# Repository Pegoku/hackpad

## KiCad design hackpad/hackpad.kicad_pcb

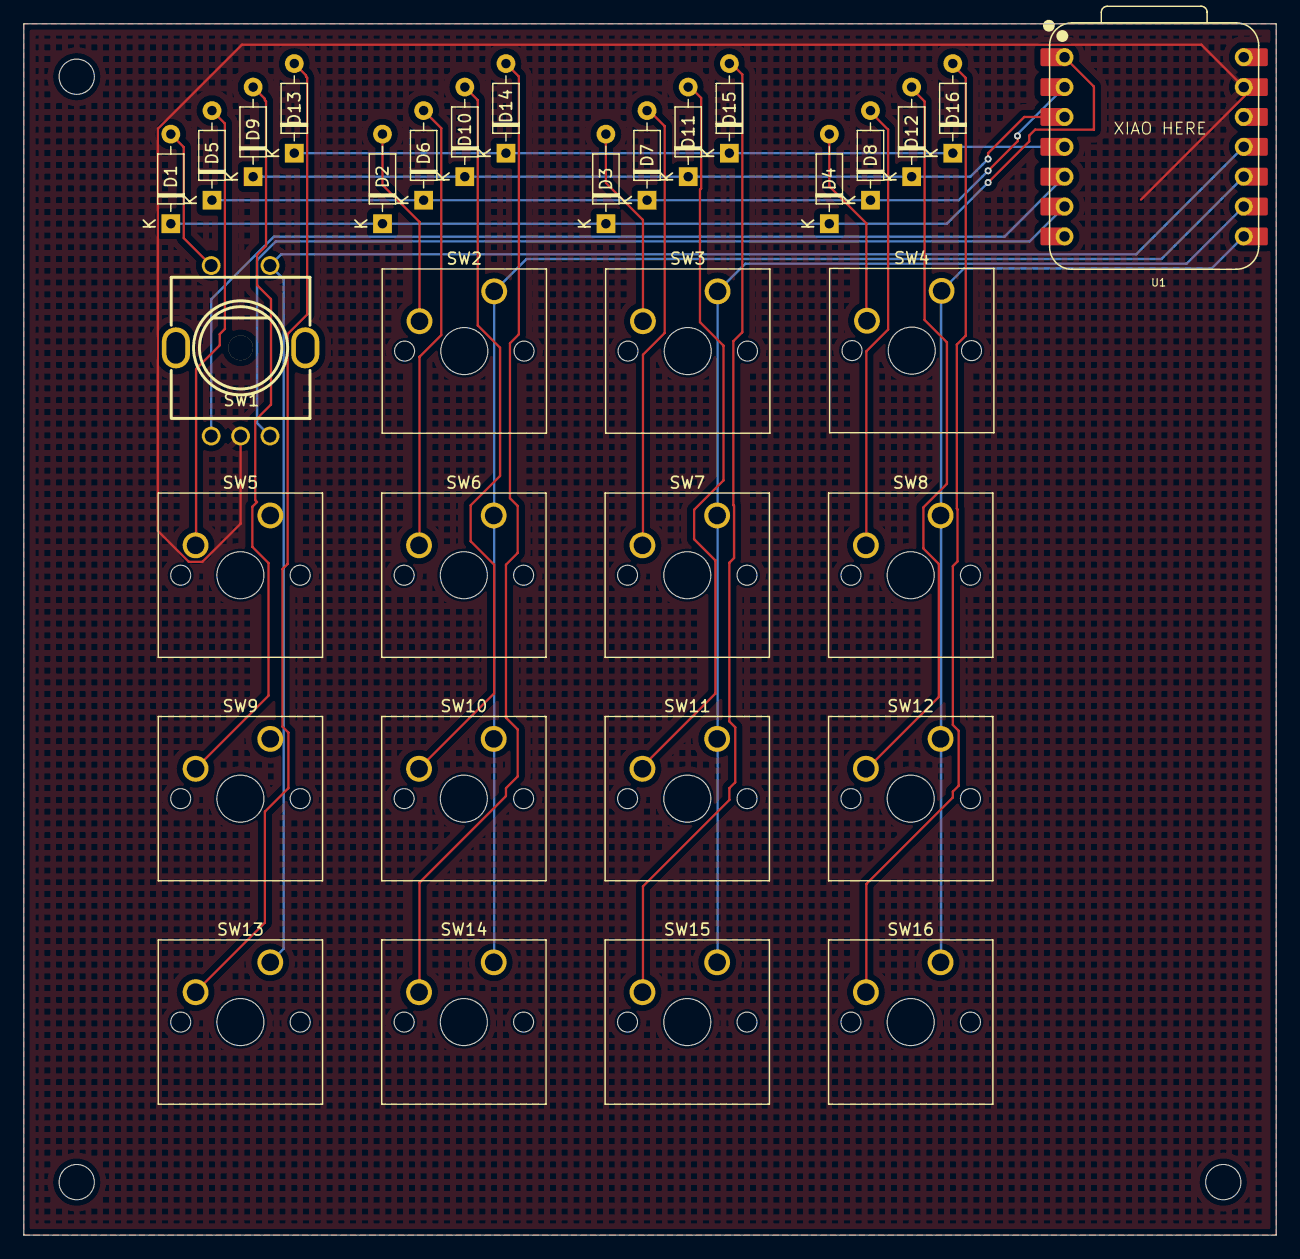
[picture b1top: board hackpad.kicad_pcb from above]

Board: 2 copper layers, 106.5 x 103.0 mm, 33 parts (0 on the bottom side), 27 nets.

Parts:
D1, D2, D3, D4, D5, D6, D7, D8, D9, D10, D11, D12, D13, D14, D15, D16: 1N4148; D_DO-35_SOD27_P7.62mm_Horizontal
SW1: EC11G1534414; SW-TH_EC11G1534414
SW2, SW3, SW4, SW5, SW6, SW7, SW8, SW9, SW10, SW11, SW12, SW13, SW14, SW15, SW16: SW_Push; SW_Cherry_MX_1.00u_PCB
U1: MOUDLE-SEEEDUINO-XIAO; XIAO-RP2040-DIP

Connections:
A: SW1.A, U1.5 (PA8_A4_D4_SDA)
B: SW1.B, U1.6 (PA9_A5_D5_SCL)
C1: SW1.E, SW5.1, SW9.1, SW13.1, U1.11 (PA6_A10_D10_MOSI)
C2: SW2.1, SW6.1, SW10.1, SW14.1, U1.10 (PA5_A9_D9_MISO)
C3: SW3.1, SW7.1, SW11.1, SW15.1, U1.9 (PA7_A8_D8_SCK)
C4: SW4.1, SW8.1, SW12.1, SW16.1, U1.8 (PB09_A7_D7_RX)
GND: SW1.C, U1.13 (GND)
unnamed: D1.2 (A), SW1.D
unnamed: D2.2 (A), SW2.2
unnamed: D3.2 (A), SW3.2
unnamed: D4.2 (A), SW4.2
unnamed: D5.2 (A), SW5.2
unnamed: D6.2 (A), SW6.2
unnamed: D7.2 (A), SW7.2
unnamed: D8.2 (A), SW8.2
unnamed: D9.2 (A), SW9.2
unnamed: D10.2 (A), SW10.2
unnamed: D11.2 (A), SW11.2
unnamed: D12.2 (A), SW12.2
unnamed: D13.2 (A), SW13.2
unnamed: D14.2 (A), SW14.2
unnamed: D15.2 (A), SW15.2
unnamed: D16.2 (A), SW16.2
R1: D1.1 (K), D2.1 (K), D3.1 (K), D4.1 (K), U1.1 (PA02_A0_D0)
R2: D5.1 (K), D6.1 (K), D7.1 (K), D8.1 (K), U1.2 (PA4_A1_D1)
R3: D9.1 (K), D10.1 (K), D11.1 (K), D12.1 (K), U1.3 (PA10_A2_D2)
R4: D13.1 (K), D14.1 (K), D15.1 (K), D16.1 (K), U1.4 (PA11_A3_D3)

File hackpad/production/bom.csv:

Designator,Footprint,Quantity,Value,LCSC Part #
"D1, D10, D11, D12, D13, D14, D15, D16, D2, D3, D4, D5, D6, D7, D8, D9",D_DO-35_SOD27_P7.62mm_Horizontal,16,1N4148,
SW1,SW-TH_EC11G1534414,1,EC11G1534414,C1322547
"SW10, SW11, SW12, SW13, SW14, SW15, SW16, SW2, SW3, SW4, SW5, SW6, SW7, SW8, SW9",SW_Cherry_MX_1.00u_PCB,15,SW_Push,
U1,XIAO-RP2040-DIP,1,MOUDLE-SEEEDUINO-XIAO,

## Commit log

2025-02-13 finish
